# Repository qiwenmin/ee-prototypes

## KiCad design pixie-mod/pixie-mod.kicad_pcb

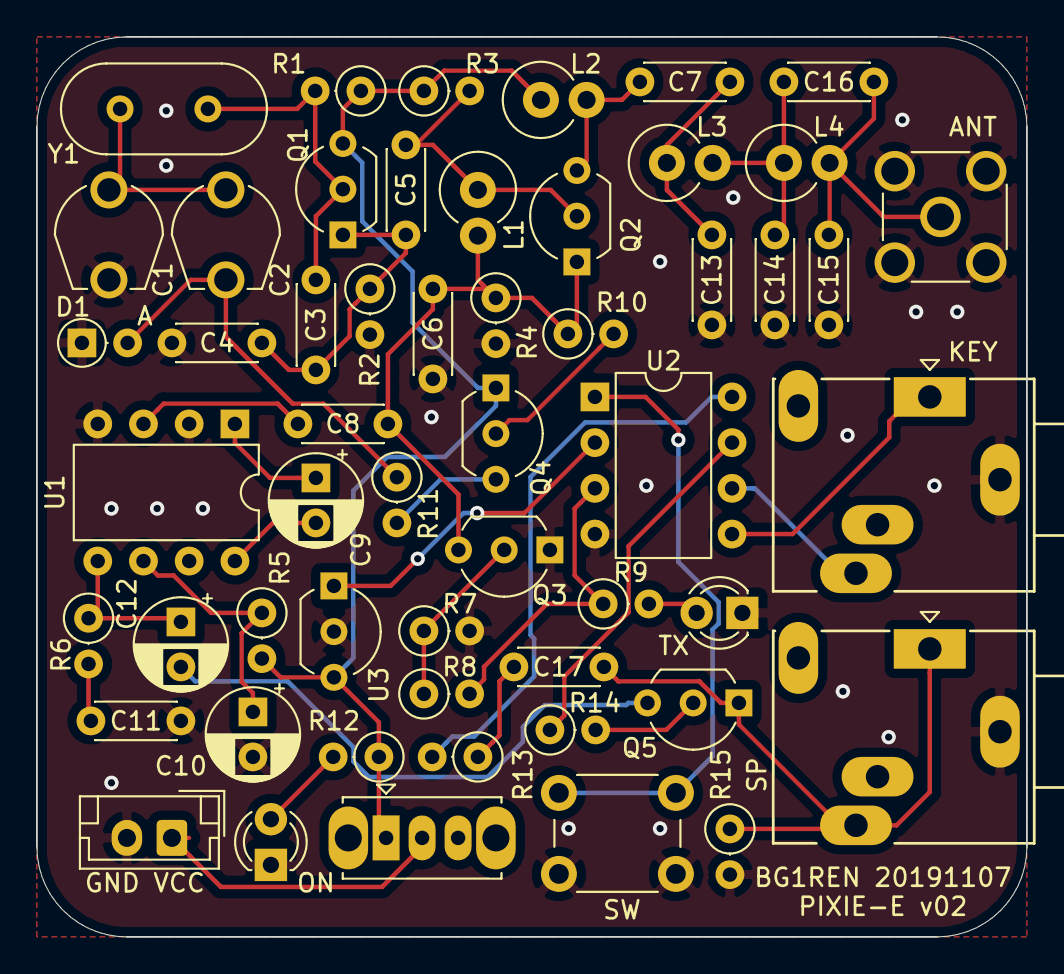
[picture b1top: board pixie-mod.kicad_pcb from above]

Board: 2 copper layers, 55.0 x 50.0 mm, 54 parts (0 on the bottom side), 35 nets.

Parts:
C1: 60; TZ03-F
C2: 40; TZ03-F
C3, C4, C16: 100; C_Disc_D4.3mm_W1.9mm_P5.00mm
C5, C7, C11: 10n; C_Disc_D4.3mm_W1.9mm_P5.00mm
C6: 47n; C_Disc_D4.3mm_W1.9mm_P5.00mm
C8, C17: 100n; C_Disc_D4.3mm_W1.9mm_P5.00mm
C9, C12: 10u; CP_Radial_D5.0mm_P2.50mm
C10: 100u; CP_Radial_D5.0mm_P2.50mm
C13, C15: 470; C_Disc_D4.3mm_W1.9mm_P5.00mm
C14: 1n; C_Disc_D4.3mm_W1.9mm_P5.00mm
D1: 1N4148; D_DO-35_SOD27_P2.54mm_Vertical_AnodeUp
D2: RED; LED_D3.0mm
D3: YELLO; LED_D3.0mm
J1: PWR; JST_EH_B2B-EH-A_1x02_P2.50mm_Vertical
J2: ANT; SMA_Molex_73251-2200_Horizontal
J3: SP; Jack_3.5mm_Ledino_KB3SPRS_Horizontal
J4: KEY; Jack_3.5mm_Ledino_KB3SPRS_Horizontal
L1: 100u; L_Axial_L9.5mm_D4.0mm_P2.54mm_Vertical_Fastron_SMCC
L2: 22u; L_Axial_L9.5mm_D4.0mm_P2.54mm_Vertical_Fastron_SMCC
L3, L4: 1u; L_Axial_L9.5mm_D4.0mm_P2.54mm_Vertical_Fastron_SMCC
Q1: 9018; TO-92_Inline_Wide
Q2, Q3: 2N2222; TO-92_Inline_Wide
Q4: 2N3906; TO-92_Inline_Wide
Q5: 2N7000; TO-92_Inline_Wide
R1, R3: 47K; R_Axial_DIN0207_L6.3mm_D2.5mm_P2.54mm_Vertical
R2: 470; R_Axial_DIN0207_L6.3mm_D2.5mm_P2.54mm_Vertical
R4, R14: 10K; R_Axial_DIN0207_L6.3mm_D2.5mm_P2.54mm_Vertical
R5, R8: 1K; R_Axial_DIN0207_L6.3mm_D2.5mm_P2.54mm_Vertical
R6: 10; R_Axial_DIN0207_L6.3mm_D2.5mm_P2.54mm_Vertical
R7, R9: 2K; R_Axial_DIN0207_L6.3mm_D2.5mm_P2.54mm_Vertical
R10, R11, R12, R13: 4.7K; R_Axial_DIN0207_L6.3mm_D2.5mm_P2.54mm_Vertical
R15: 100; R_Axial_DIN0207_L6.3mm_D2.5mm_P2.54mm_Vertical
SW1: PWR; SW_Slide_1P2T_CK_OS102011MS2Q
SW2: SW; SW_PUSH_6mm
U1: LM386; DIP-8_W7.62mm
U2: STC15W104; DIP-8_W7.62mm
U3: LM78L05_TO92; TO-92_Inline_Wide
Y1: 7.023MHz; Crystal_HC49-4H_Vertical

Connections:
5V: U2.2, U3.1
/V+: C10.1, R5.1, U1.6
AF: C12.2, Q5.3
ANT: C15.2, C16.1, J2.1, L4.2
DAH: J4.R, U2.6
DIT: J4.T, U2.5
GND: C1.2, C4.2, C6.2, C10.2, C11.1, C13.1, C14.1, C15.1, D1.1, D2.1, D3.1, J1.2, J2.2, J3.S, J4.S, Q3.1, R2.2, R4.2, R7.2, R15.2, SW2.2, U1.2, U1.4, U2.4, U3.2
KEY: C6.1, C8.1, L1.2, Q2.1, Q3.3, R4.1, R10.1
LPF: C7.1, C13.2, L3.1
MUTE: R14.1, U2.7
unnamed: C1.1, C2.1, Y1.2
unnamed: C3.1, Q1.2, R1.2, Y1.1
unnamed: C3.2, C4.1, C5.2, Q1.1, R2.1
unnamed: C5.1, L1.1, Q2.2, R3.2
unnamed: C7.2, L2.2, Q2.3
unnamed: C8.2, U1.3
unnamed: C9.1, U1.1
unnamed: C9.2, U1.8
unnamed: C11.2, R6.2
unnamed: C12.1, R6.1, U1.5
unnamed: C14.2, C16.2, L3.2, L4.1
unnamed: C17.2, R13.1
unnamed: D2.2, R9.2
unnamed: D3.2, R12.2
unnamed: J1.1, SW1.2
unnamed: Q3.2, R7.1, R8.1
unnamed: Q4.2, R10.2
unnamed: Q4.3, R11.2
unnamed: Q5.2, R14.2
unnamed: R8.2, R9.1, U2.3
Phone: C17.1, J3.R, J3.T, Q5.1, R15.1
SHIFT: C2.2, D1.2, R11.1
SW: SW2.1, U2.1
Sidetone: R13.2, U2.8
VCC: L2.1, Q1.3, Q4.1, R1.1, R3.1, R5.2, R12.1, SW1.1, U3.3

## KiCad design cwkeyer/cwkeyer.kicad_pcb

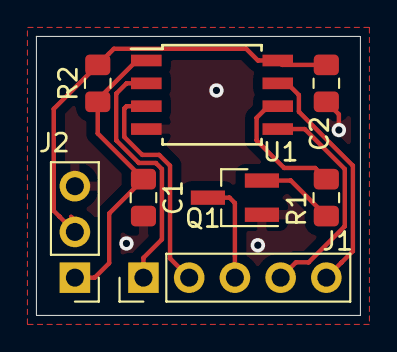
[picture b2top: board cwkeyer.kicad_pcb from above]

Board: 2 copper layers, 18.0 x 15.5 mm, 8 parts (0 on the bottom side), 10 nets.

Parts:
C1, C2: 10u; C_0805_2012Metric_Pad1.15x1.40mm_HandSolder
J1: Conn_01x05; PinHeader_1x05_P2.54mm_Vertical
J2: Conn_01x03; PinHeader_1x03_P2.54mm_Vertical
Q1: S8050; SOT-23_Handsoldering
R1, R2: 4.7K; R_0805_2012Metric_Pad1.15x1.40mm_HandSolder
U1: ATtiny85-20SU; SOIJ-8_5.3x5.3mm_P1.27mm

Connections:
GND: C1.2, C2.2, J2.3, Q1.1, U1.4
KEY: J1.3, Q1.3
unnamed: Q1.2, R1.1
unnamed: R1.2, U1.6
PAD_L: J1.1, U1.2
PAD_R: J1.2, U1.3
RESET: C1.1, J2.1, R2.1, U1.1
SW: J1.4, U1.5
TONE: J1.5, U1.7
VCC: C2.1, J2.2, R2.2, U1.8

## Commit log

2019-05-21 Change R1 from 1K to 4.7K
2019-05-21 Add C2 between VCC and GND. Reroute the PCB.
2019-05-22 Add PCB dimensions
2019-05-22 Update page settings.
2019-06-09 Re-route the PCB.
2019-07-07 Add pixie mod.
2019-07-07 Fix: the output power is too low. Now it outputs 600mW @12V.
2019-07-07 Change the value of some transistors.
2019-07-08 Add side tone.
2019-10-30 Add stckeyer to pixie.
2019-11-03 Resolve some issues with the 1st PCB.
    * Remove a short circuit
    * Fix the footprint of C1/C2
    * Change R4 to 470
2019-11-04 Modify some values as the last working board.
2019-11-05 Update the schematic as the last working board.
2019-11-10 Final v02
2019-11-18 Add/Update some comments.
